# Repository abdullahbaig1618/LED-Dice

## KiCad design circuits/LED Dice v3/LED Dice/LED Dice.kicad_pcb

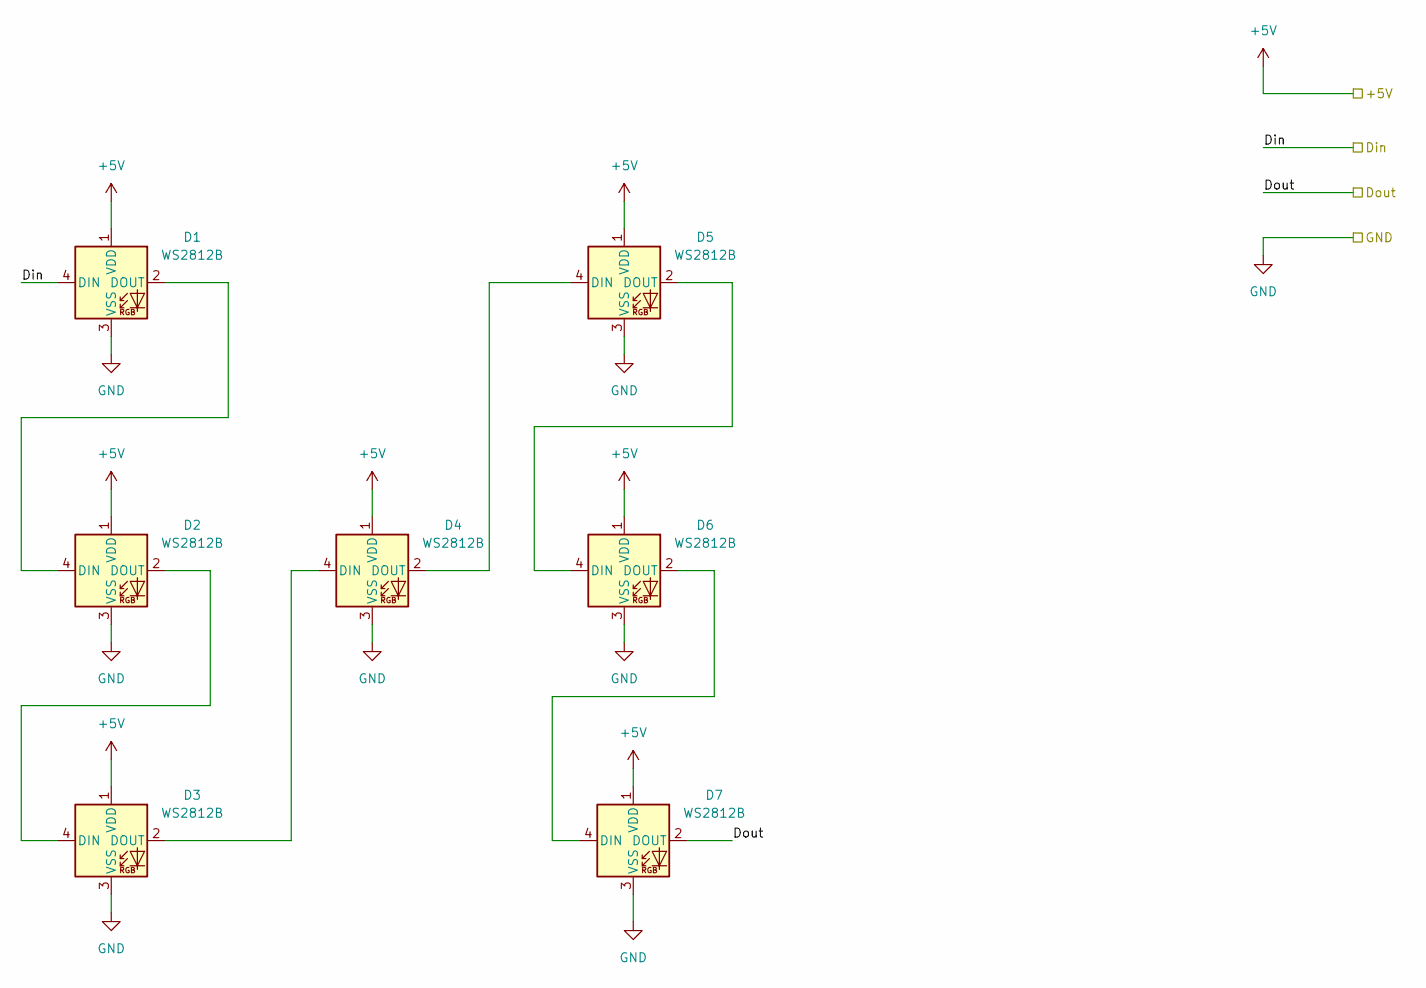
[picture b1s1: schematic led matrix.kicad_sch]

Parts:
D1, D2, D3, D4, D5, D6, D7: WS2812B; LED_WS2812B_PLCC4_5.0x5.0mm_P3.2mm; Part No WS2812B-B/W

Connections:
+5V: D1.1 (VDD), D2.1 (VDD), D3.1 (VDD), D4.1 (VDD), D5.1 (VDD), D6.1 (VDD), D7.1 (VDD); also elsewhere on the board
/LED Matrix 2/Din: D7.2 (DOUT); also elsewhere on the board
/LED matrix 1/Din: D1.4 (DIN); also elsewhere on the board
GND: D1.3 (VSS), D2.3 (VSS), D3.3 (VSS), D4.3 (VSS), D5.3 (VSS), D6.3 (VSS), D7.3 (VSS); also elsewhere on the board
unnamed: D1.2 (DOUT), D2.4 (DIN)
unnamed: D2.2 (DOUT), D3.4 (DIN)
unnamed: D3.2 (DOUT), D4.4 (DIN)
unnamed: D4.2 (DOUT), D5.4 (DIN)
unnamed: D5.2 (DOUT), D6.4 (DIN)
unnamed: D6.2 (DOUT), D7.4 (DIN)

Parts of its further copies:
D8, D9, D10, D11, D12, D13, D14: WS2812B; LED_WS2812B_PLCC4_5.0x5.0mm_P3.2mm; Part No WS2812B-B/W

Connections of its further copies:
+5V: D8.1 (VDD), D9.1 (VDD), D10.1 (VDD), D11.1 (VDD), D12.1 (VDD), D13.1 (VDD), D14.1 (VDD); also elsewhere on the board
/LED Matrix 2/Din: D8.4 (DIN); also elsewhere on the board
/LED Matrix 2/Dout: D14.2 (DOUT)
GND: D8.3 (VSS), D9.3 (VSS), D10.3 (VSS), D11.3 (VSS), D12.3 (VSS), D13.3 (VSS), D14.3 (VSS); also elsewhere on the board
unnamed: D8.2 (DOUT), D9.4 (DIN)
unnamed: D9.2 (DOUT), D10.4 (DIN)
unnamed: D10.2 (DOUT), D11.4 (DIN)
unnamed: D11.2 (DOUT), D12.4 (DIN)
unnamed: D12.2 (DOUT), D13.4 (DIN)
unnamed: D13.2 (DOUT), D14.4 (DIN)

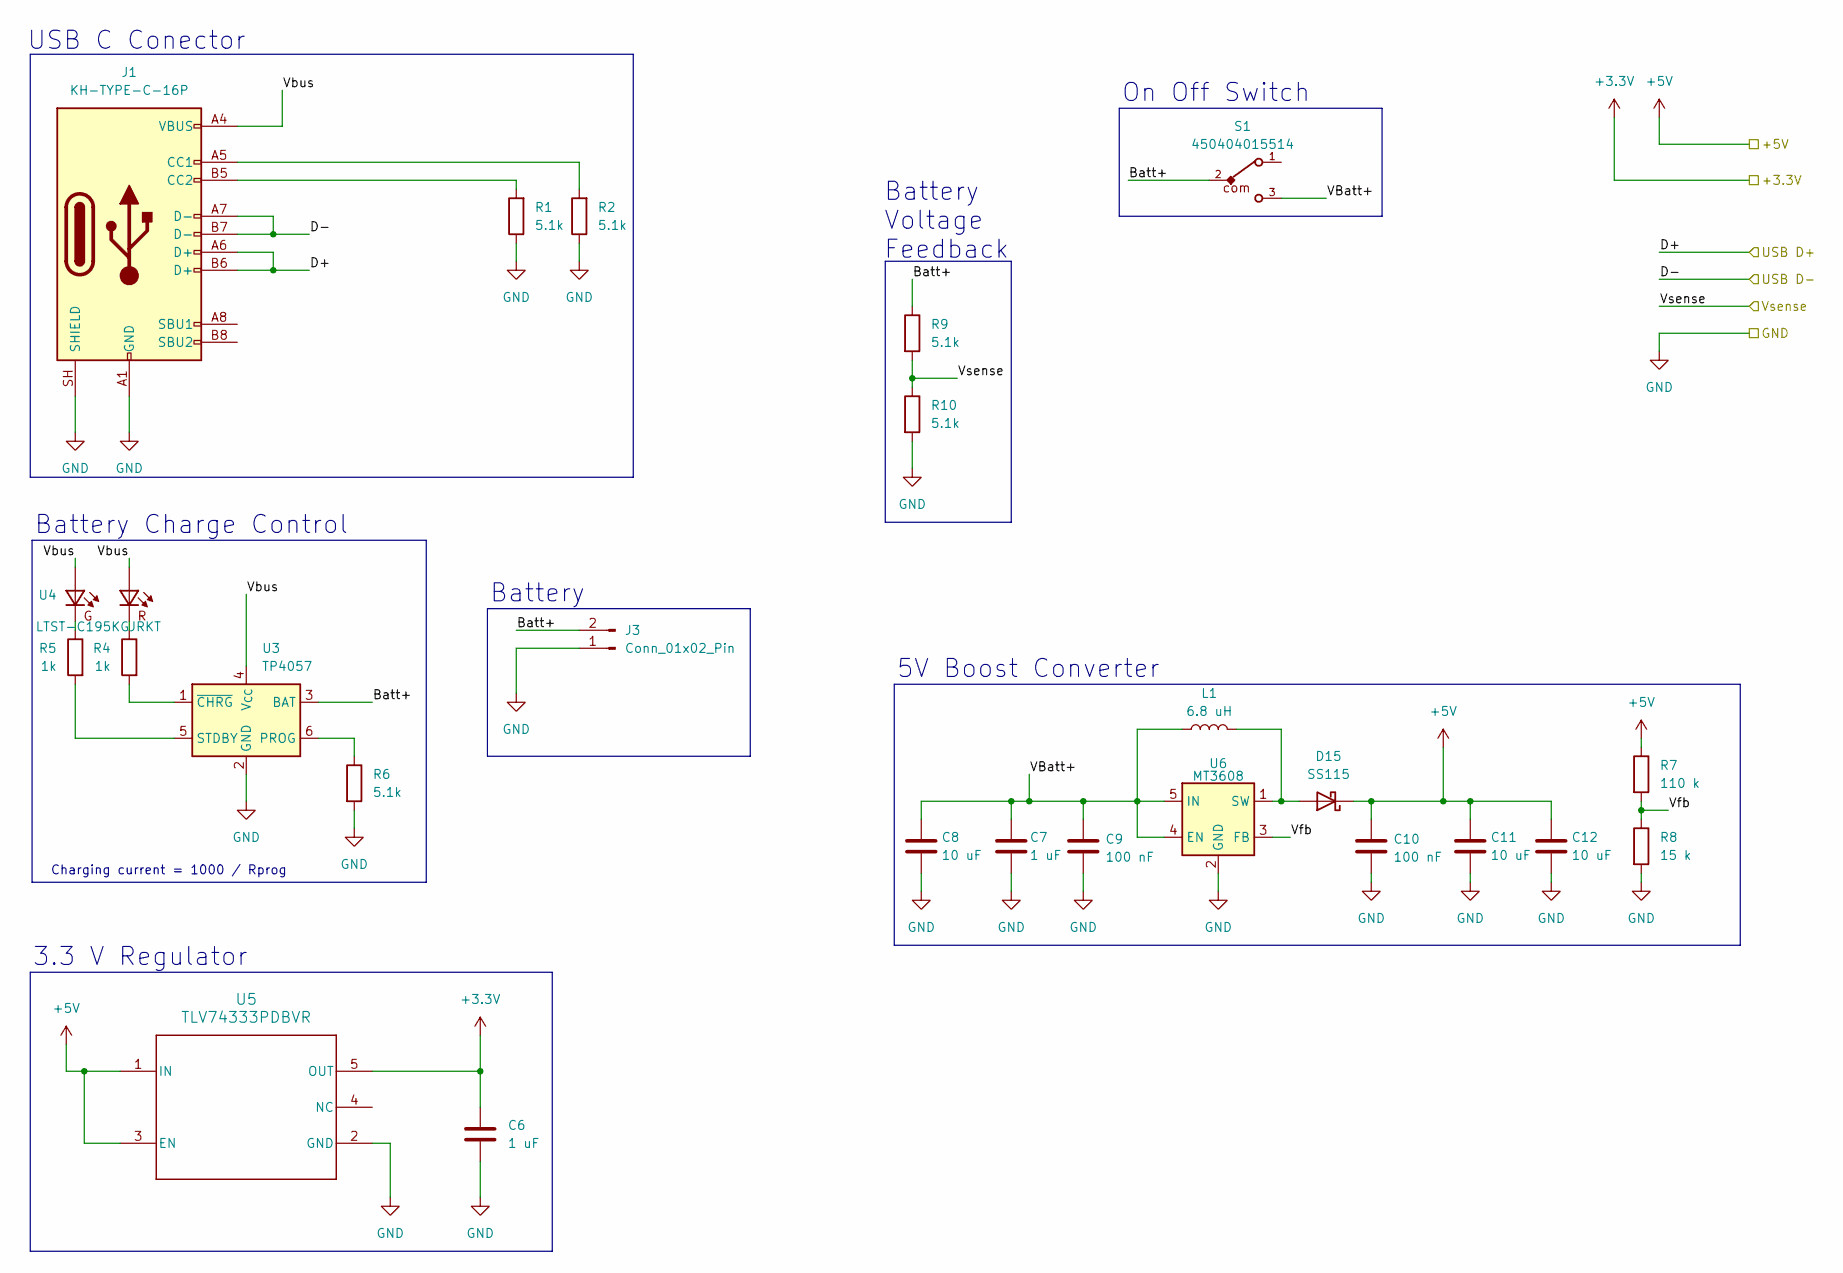
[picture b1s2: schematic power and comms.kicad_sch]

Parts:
C6: 1 uF; C_0603_1608Metric_Pad1.08x0.95mm_HandSolder; Part No CL10B105KB8NQNC
C7: 1 uF; C_0805_2012Metric_Pad1.18x1.45mm_HandSolder; Part No CL21B105KBFNNNE
C8, C12: 10 uF; C_1206_3216Metric_Pad1.33x1.80mm_HandSolder; Part No CL31A106KAHNNNE
C9, C10: 100 nF; C_0603_1608Metric_Pad1.08x0.95mm_HandSolder; Part No CL10B104KB8NNNC
C11: 10 uF; C_0805_2012Metric_Pad1.18x1.45mm_HandSolder; Part No CL31A106KAHNNNE
D15: SS115; D_SMA_Handsoldering; Part No SS115
J1: KH-TYPE-C-16P; USB_C_Receptacle_GCT_USB4105-xx-A_16P_TopMnt_Horizontal; Part No KH-TYPE-C-16P
J3: Conn_01x02_Pin; PinHeader_1x02_P2.54mm_Vertical; Part No PZ254V-11-02P
L1: 6.8 uH; L_Changjiang_FXL0412; Part No FXL0420-6R8-M
R1: 5.1k; R_0603_1608Metric; Part No FRC0603F5101TS
R2, R6, R9, R10: 5.1k; R_0603_1608Metric_Pad0.98x0.95mm_HandSolder; Part No FRC0603F5101TS
R4, R5: 1k; R_0603_1608Metric_Pad0.98x0.95mm_HandSolder; Part No FRC0603F1001TS
R7: 110 k; R_0603_1608Metric_Pad0.98x0.95mm_HandSolder; Part No FRC0603F1103TS
R8: 15 k; R_0603_1608Metric_Pad0.98x0.95mm_HandSolder; Part No FRC0603F1502TS
S1: 450404015514; Part No MK-12C02-G020
U3: TP4057; TSOT-23-6; Part No TP4057
U4: LTST-C195KGJRKT; LTST-BILED-15X16; Part No LTST-C195KGJRKT
U5: TLV74333PDBVR; DBV0005A_M; Part No TLV74333PDBVR
U6: MT3608; SOT-23-6; Part No MT3608

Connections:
+3.3V: C6.1, U5.5 (OUT); also elsewhere on the board
+5V: C10.1, C11.1, C12.1, D15.1 (K), R7.1, U5.1 (IN), U5.3 (EN); also elsewhere on the board
/Microcontroller/USB D+: J1.A6 (D+), J1.B6 (D+); also elsewhere on the board
/Microcontroller/USB D-: J1.A7 (D-), J1.B7 (D-); also elsewhere on the board
/Microcontroller/Vsample: R9.2, R10.1; also elsewhere on the board
/Power and Comms/Batt+: J3.2, R9.1, S1.2, U3.3 (BAT)
/Power and Comms/VBatt+: C7.1, C8.1, C9.1, L1.1, S1.3, U6.4 (EN), U6.5 (IN)
/Power and Comms/Vbus: J1.A4 (VBUS), J1.A9 (VBUS), J1.B4 (VBUS), J1.B9 (VBUS), U3.4 (V_{CC}), U4.P$1, U4.P$2
/Power and Comms/Vfb: R7.2, R8.1, U6.3 (FB)
GND: C6.2, C7.2, C8.2, C9.2, C10.2, C11.2, C12.2, J1.A1 (GND), J1.A12 (GND), J1.B1 (GND), J1.B12 (GND), J1.SH (SHIELD), J3.1, R1.1, R2.1, R6.2, R8.2, R10.2, U3.2 (GND), U5.2 (GND), U6.2 (GND); also elsewhere on the board
unnamed: D15.2 (A), L1.2, U6.1 (SW)
unnamed: J1.A5 (CC1), R2.2
unnamed: J1.B5 (CC2), R1.2
unnamed: R4.1, U4.P$4
unnamed: R5.1, U4.P$3
unnamed: R6.1, U3.6 (PROG)
unnamed: R5.2, U3.5 (STDBY)
unnamed: R4.2, U3.1 (~CHRG)

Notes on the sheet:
Charging current = 1000 / Rprog
Battery Voltage Feedback
5V Boost Converter
Battery
On Off Switch
Battery Charge Control
USB C Conector
3.3 V Regulator

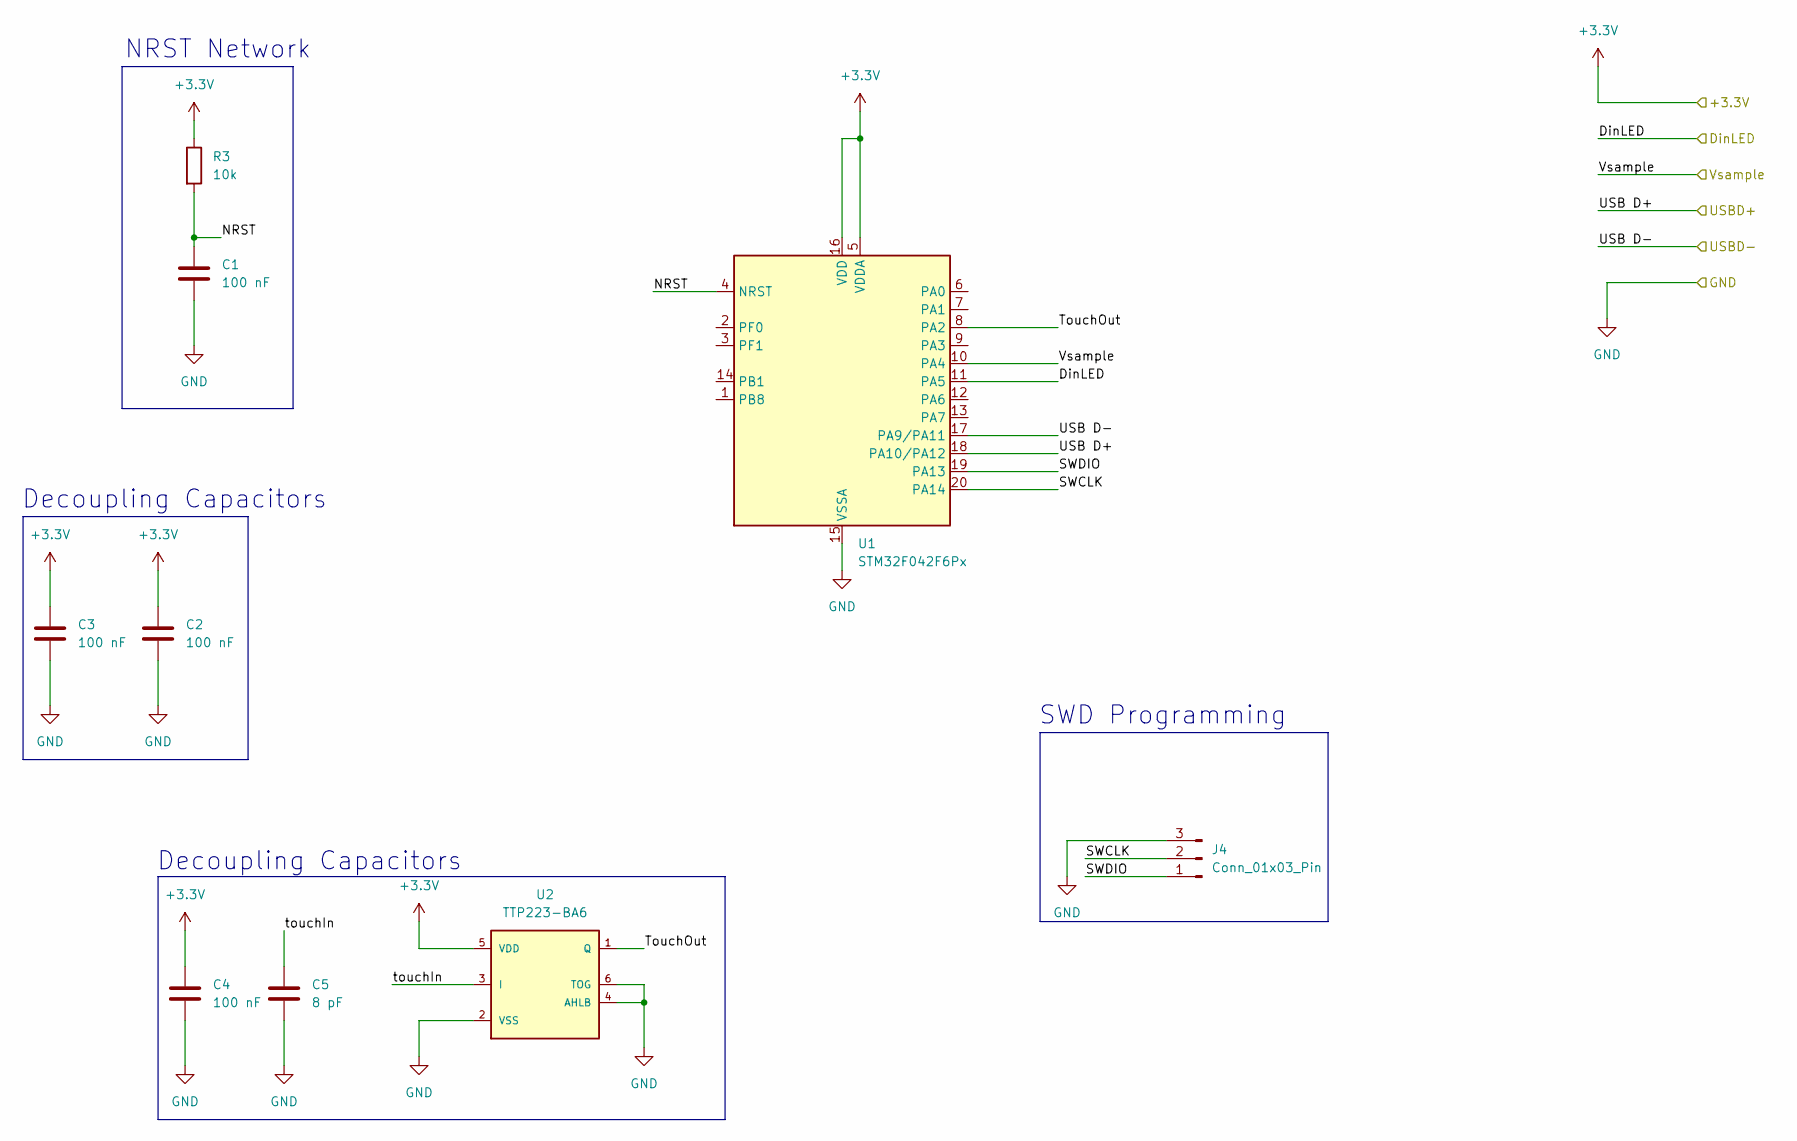
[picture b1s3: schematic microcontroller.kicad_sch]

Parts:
C1, C2, C3, C4: 100 nF; C_0603_1608Metric_Pad1.08x0.95mm_HandSolder; Part No CL10B104KB8NNNC
C5: 8 pF; C_0603_1608Metric_Pad1.08x0.95mm_HandSolder; Part No CL10C080DB81PNC
J4: Conn_01x03_Pin; PinHeader_1x03_P2.54mm_Vertical; Part No HX PZ2.54-1x4P ZZ
R3: 10k; R_0603_1608Metric_Pad0.98x0.95mm_HandSolder; Part No FRC0603J103 TS
U1: STM32F042F6Px; TSSOP-20_4.4x6.5mm_P0.65mm; Part No STM32F042F6P6TR
U2: TTP223-BA6; SOT23-6; Part No TTP223-BA6

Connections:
+3.3V: C2.1, C3.1, C4.1, R3.1, U1.5 (VDDA), U1.16 (VDD), U2.5 (VDD); also elsewhere on the board
/LED matrix 1/Din: U1.11 (PA5); also elsewhere on the board
/Microcontroller/NRST: C1.1, R3.2, U1.4 (NRST)
/Microcontroller/SWCLK: J4.2, U1.20 (PA14)
/Microcontroller/SWDIO: J4.1, U1.19 (PA13)
/Microcontroller/TouchOut: U1.8 (PA2), U2.1 (Q)
/Microcontroller/USB D+: U1.18 (PA10/PA12); also elsewhere on the board
/Microcontroller/USB D-: U1.17 (PA9/PA11); also elsewhere on the board
/Microcontroller/Vsample: U1.10 (PA4); also elsewhere on the board
/Microcontroller/touchIn: C5.1, U2.3 (I)
GND: C1.2, C2.2, C3.2, C4.2, C5.2, J4.3, U1.15 (VSSA), U2.2 (VSS), U2.4 (AHLB), U2.6 (TOG); also elsewhere on the board

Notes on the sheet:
Decoupling Capacitors
SWD Programming
NRST Network

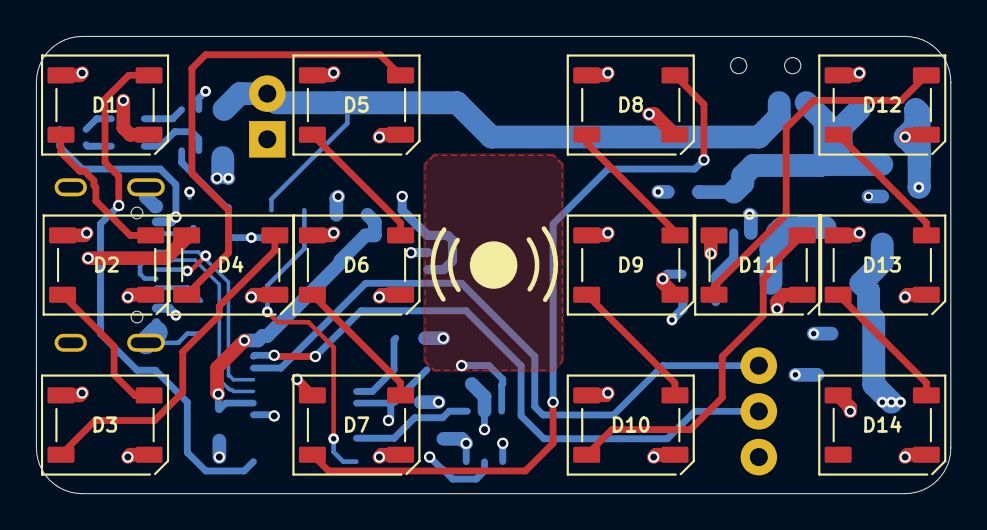
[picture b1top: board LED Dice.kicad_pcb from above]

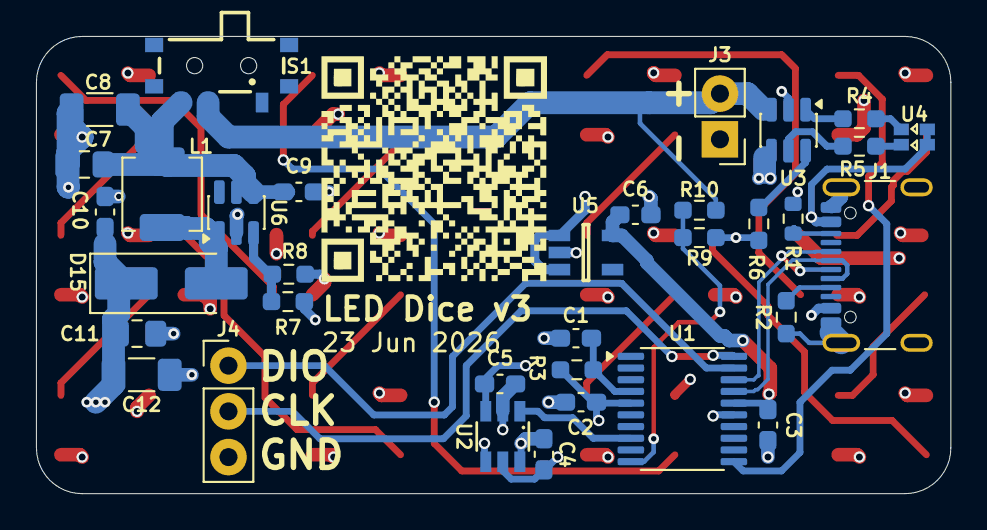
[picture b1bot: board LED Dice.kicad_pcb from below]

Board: 4 copper layers, 50.8 x 25.4 mm, 48 parts (34 on the bottom side), 37 nets.

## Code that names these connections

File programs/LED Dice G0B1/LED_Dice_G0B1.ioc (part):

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Mcu.Name=STM32G0B1C(B-C-E)Tx
Mcu.Package=LQFP48
Mcu.UserName=STM32G0B1CBTx
PA0.Signal=S_TIM2_CH1_ETR
PA11\ [PA9].Mode=Device
PA11\ [PA9].Signal=USB_DM
PA12\ [PA10].Mode=Device
PA12\ [PA10].Signal=USB_DP
PA13.Mode=Serial_Wire
PA13.Signal=SYS_SWDIO
PA14-BOOT0.Mode=Serial_Wire
PA14-BOOT0.Signal=SYS_SWCLK
PA4.GPIOParameters=GPIO_Label
PA4.GPIO_Label=Vbatt
PA4.Mode=IN4
PA4.Signal=ADC1_IN4
RCC.HSE_VALUE=8000000
RCC.SYSCLKFreq_VALUE=16000000
RCC.SYSCLKSource=RCC_SYSCLKSOURCE_PLLCLK
board=custom

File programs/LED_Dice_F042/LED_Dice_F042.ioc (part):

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Mcu.Name=STM32F042F6Px
Mcu.Package=TSSOP20
Mcu.UserName=STM32F042F6Px
PA13.Mode=Serial_Wire
PA13.Signal=SYS_SWDIO
PA14.Mode=Serial_Wire
PA14.Signal=SYS_SWCLK
PA2.GPIOParameters=GPIO_Label
PA2.GPIO_Label=touch
PA2.Signal=GPIO_Input
PA4.GPIOParameters=GPIO_Label
PA4.GPIO_Label=Vbatt
PA4.Mode=IN4
PA4.Signal=ADC_IN4
PA5.Signal=S_TIM2_CH1_ETR
RCC.SYSCLKFreq_VALUE=48000000
RCC.SYSCLKSource=RCC_SYSCLKSOURCE_PLLCLK
board=custom

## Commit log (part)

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2025-08-02 Add existing files
2025-08-02 Initial files upload
2025-08-02 gerbers generated
2025-08-02 libraries corrected to latest components, BOM updated
2025-08-02 updated microcontroller pins in Cube IDE project
2026-06-17 add git ignore
2026-06-17 modified G030 code for WS2812C
2026-06-17 deleted bluepill code
2026-06-20 generated schematic
2026-06-20 Make project in Kicad, use microcontroller capable of USB comms
2026-06-22 schematic is complete
2026-06-22 layout progress
2026-06-22 layout complete, some DRC violations are present
2026-06-22 All meaningful DRC resolved
2026-06-24 gerbers and BOM generated
